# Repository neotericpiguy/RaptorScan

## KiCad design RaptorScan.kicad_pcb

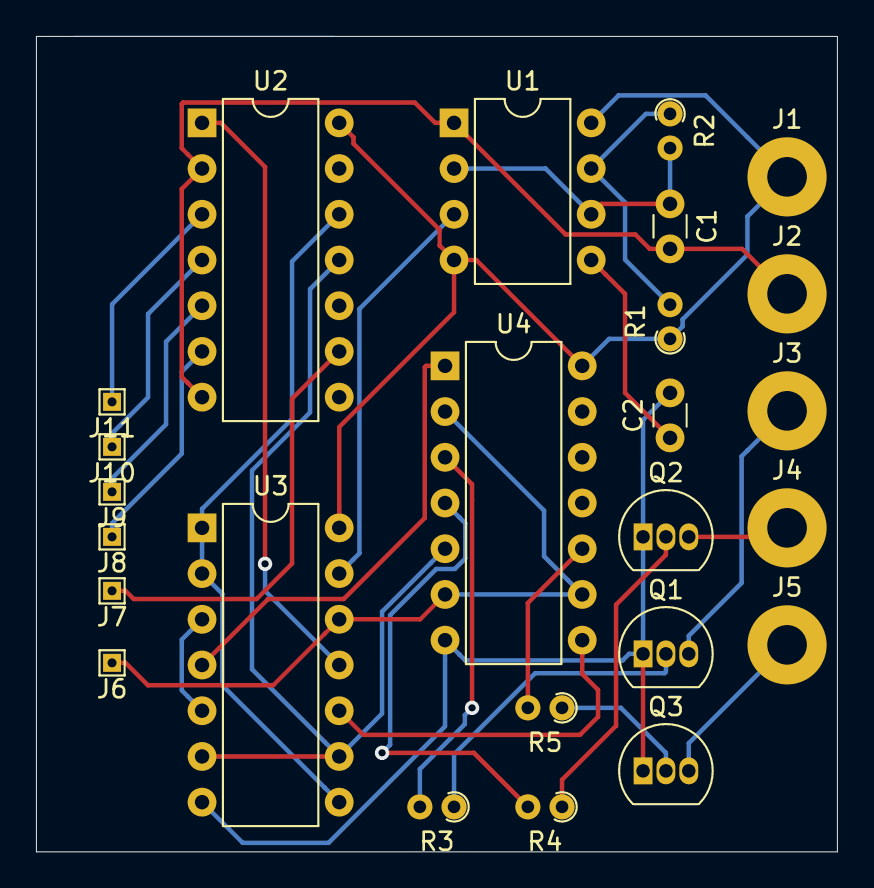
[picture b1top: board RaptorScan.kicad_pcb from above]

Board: 2 copper layers, 44.5 x 45.3 mm, 25 parts (0 on the bottom side), 27 nets.

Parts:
C1: 47uF; C_Disc_D3.0mm_W1.6mm_P2.50mm
C2: 10nf; C_Disc_D3.0mm_W1.6mm_P2.50mm
J1, J2, J3, J4, J5: Conn_01x01; MountingHole_2.2mm_M2_Pad
J6, J7, J8, J9, J10, J11: Conn_01x01_Female; TestPoint_THTPad_1.0x1.0mm_Drill0.5mm
Q1, Q2, Q3: PN2222A; TO-92_Inline
R1: 10k; R_Axial_DIN0204_L3.6mm_D1.6mm_P1.90mm_Vertical
R2: 5k; R_Axial_DIN0204_L3.6mm_D1.6mm_P1.90mm_Vertical
R3, R4, R5: R; R_Axial_DIN0204_L3.6mm_D1.6mm_P1.90mm_Vertical
U1: LM555; DIP-8_W7.62mm
U2: NTE4024; DIP-14_W7.62mm
U3: NTE4001; DIP-14_W7.62mm
U4: NTE4071; DIP-14_W7.62mm

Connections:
+12V: J1.1, R1.1, U1.4, U1.8, U2.14, U3.14, U4.14
/7BitCounter/Q0: U2.12, U3.1, U3.2, U3.8
/7BitCounter/Q1: U2.11, U3.6, U3.9, U4.5
/7BitCounter/Q2: J7.1, U2.9
/7BitCounter/Q3: J8.1, U2.6
/7BitCounter/Q4: J9.1, U2.5
/7BitCounter/Q5: J10.1, U2.4
/7BitCounter/Q6: J11.1, U2.3
/ClockProvider01/Clk: U1.3, U3.13
/LedDriver/Aout: J3.1, Q1.3
/LedDriver/Bout: J4.1, Q2.3
/LedDriver/Cout: J5.1, Q3.3
/MuxDecoder/A: R3.2, U4.3
/MuxDecoder/B: R4.2, U4.4
/MuxDecoder/C: R5.2, U4.10
/MuxDecoder/ClkOut: U2.1, U3.11
/MuxDecoder/Z: J6.1, U3.12, U4.2, U4.6, U4.9
GND: C1.2, C2.2, J2.1, Q1.1, Q2.1, Q3.1, U1.1, U2.2, U2.7, U3.7, U4.7
unnamed: C1.1, R2.2, U1.2, U1.6
unnamed: C2.1, U1.5
unnamed: Q1.2, R3.1
unnamed: Q2.2, R4.1
unnamed: Q3.2, R5.1
unnamed: R1.2, R2.1, U1.7
unnamed: U3.3, U3.5
unnamed: U3.4, U4.1
unnamed: U3.10, U4.8

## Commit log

2019-06-25 Added: 7 Bit Counter
2019-06-26 Added: MuxDecoder
2019-06-26 Added:Makefile
2019-06-26 Renamed: NTE4001
2019-06-26 Added: Makefile BOM cleaning
2019-06-26 Added: connectors
2019-06-26 Added: netlist
2019-06-26 Added: pcb
2019-06-27 Added: LedDriver
2019-07-02 Added: Mounting holes
2019-07-02 Update: BOM
2019-07-02 Moved: schs to src
2019-07-02 Updated: Makefile
2019-07-02 Updated: pdf
2019-07-02 Added: pdf sch
2019-07-02 Added: BOM
